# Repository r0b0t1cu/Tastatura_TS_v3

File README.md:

# Custom Keyboard for Turbo Spectrum

This is an open-source project for a mechanical keyboard compatible with the Romanian Turbo Spectrum computer: https://cobrasov.org/

The keyboard is designed to be easy to build, using accessible and commonly available components.
It also works with the classic ZX Spectrum, offering full compatibility with both systems.

# Keyboard PCB

The Gerber files are located in the production folder.

**Instructions for installing the required key switch libraries:**

Open the KiCad Plugin and Content Manager (PCM) and click Manage. Add a new entry with the plus button and paste the following URL:
https://raw.githubusercontent.com/ebastler/ebastler-KiCad-repository/main/repository.json

From now on, the "ebastler KiCad repository" will appear in your drop-down list, allowing you to easily install and update marbastlib directly through PCM — simple and hassle-free.

# Tastatură Custom pentru Turbo Spectrum

Acesta este un proiect open-source pentru o tastatură mecanică compatibilă cu computerul românesc **Turbo Spectrum**: https://cobrasov.org/
Tastatura a fost proiectată pentru a fi ușor de construit, utilizând componente accesibile.

Instructiuni pentru librariile de butoane folosite:
Open the KiCad "Plugin and Content Manager" (referred to as "PCM" from now on) and click on "Manage". Add a new entry with the plus sign and paste
https://raw.githubusercontent.com/ebastler/ebastler-KiCad-repository/main/repository.json
From this point on you will have "ebastler KiCad repository" in your drop-down selection, and it will allow you to install (and update) marbastlib through PCM - easy and hassle-free.

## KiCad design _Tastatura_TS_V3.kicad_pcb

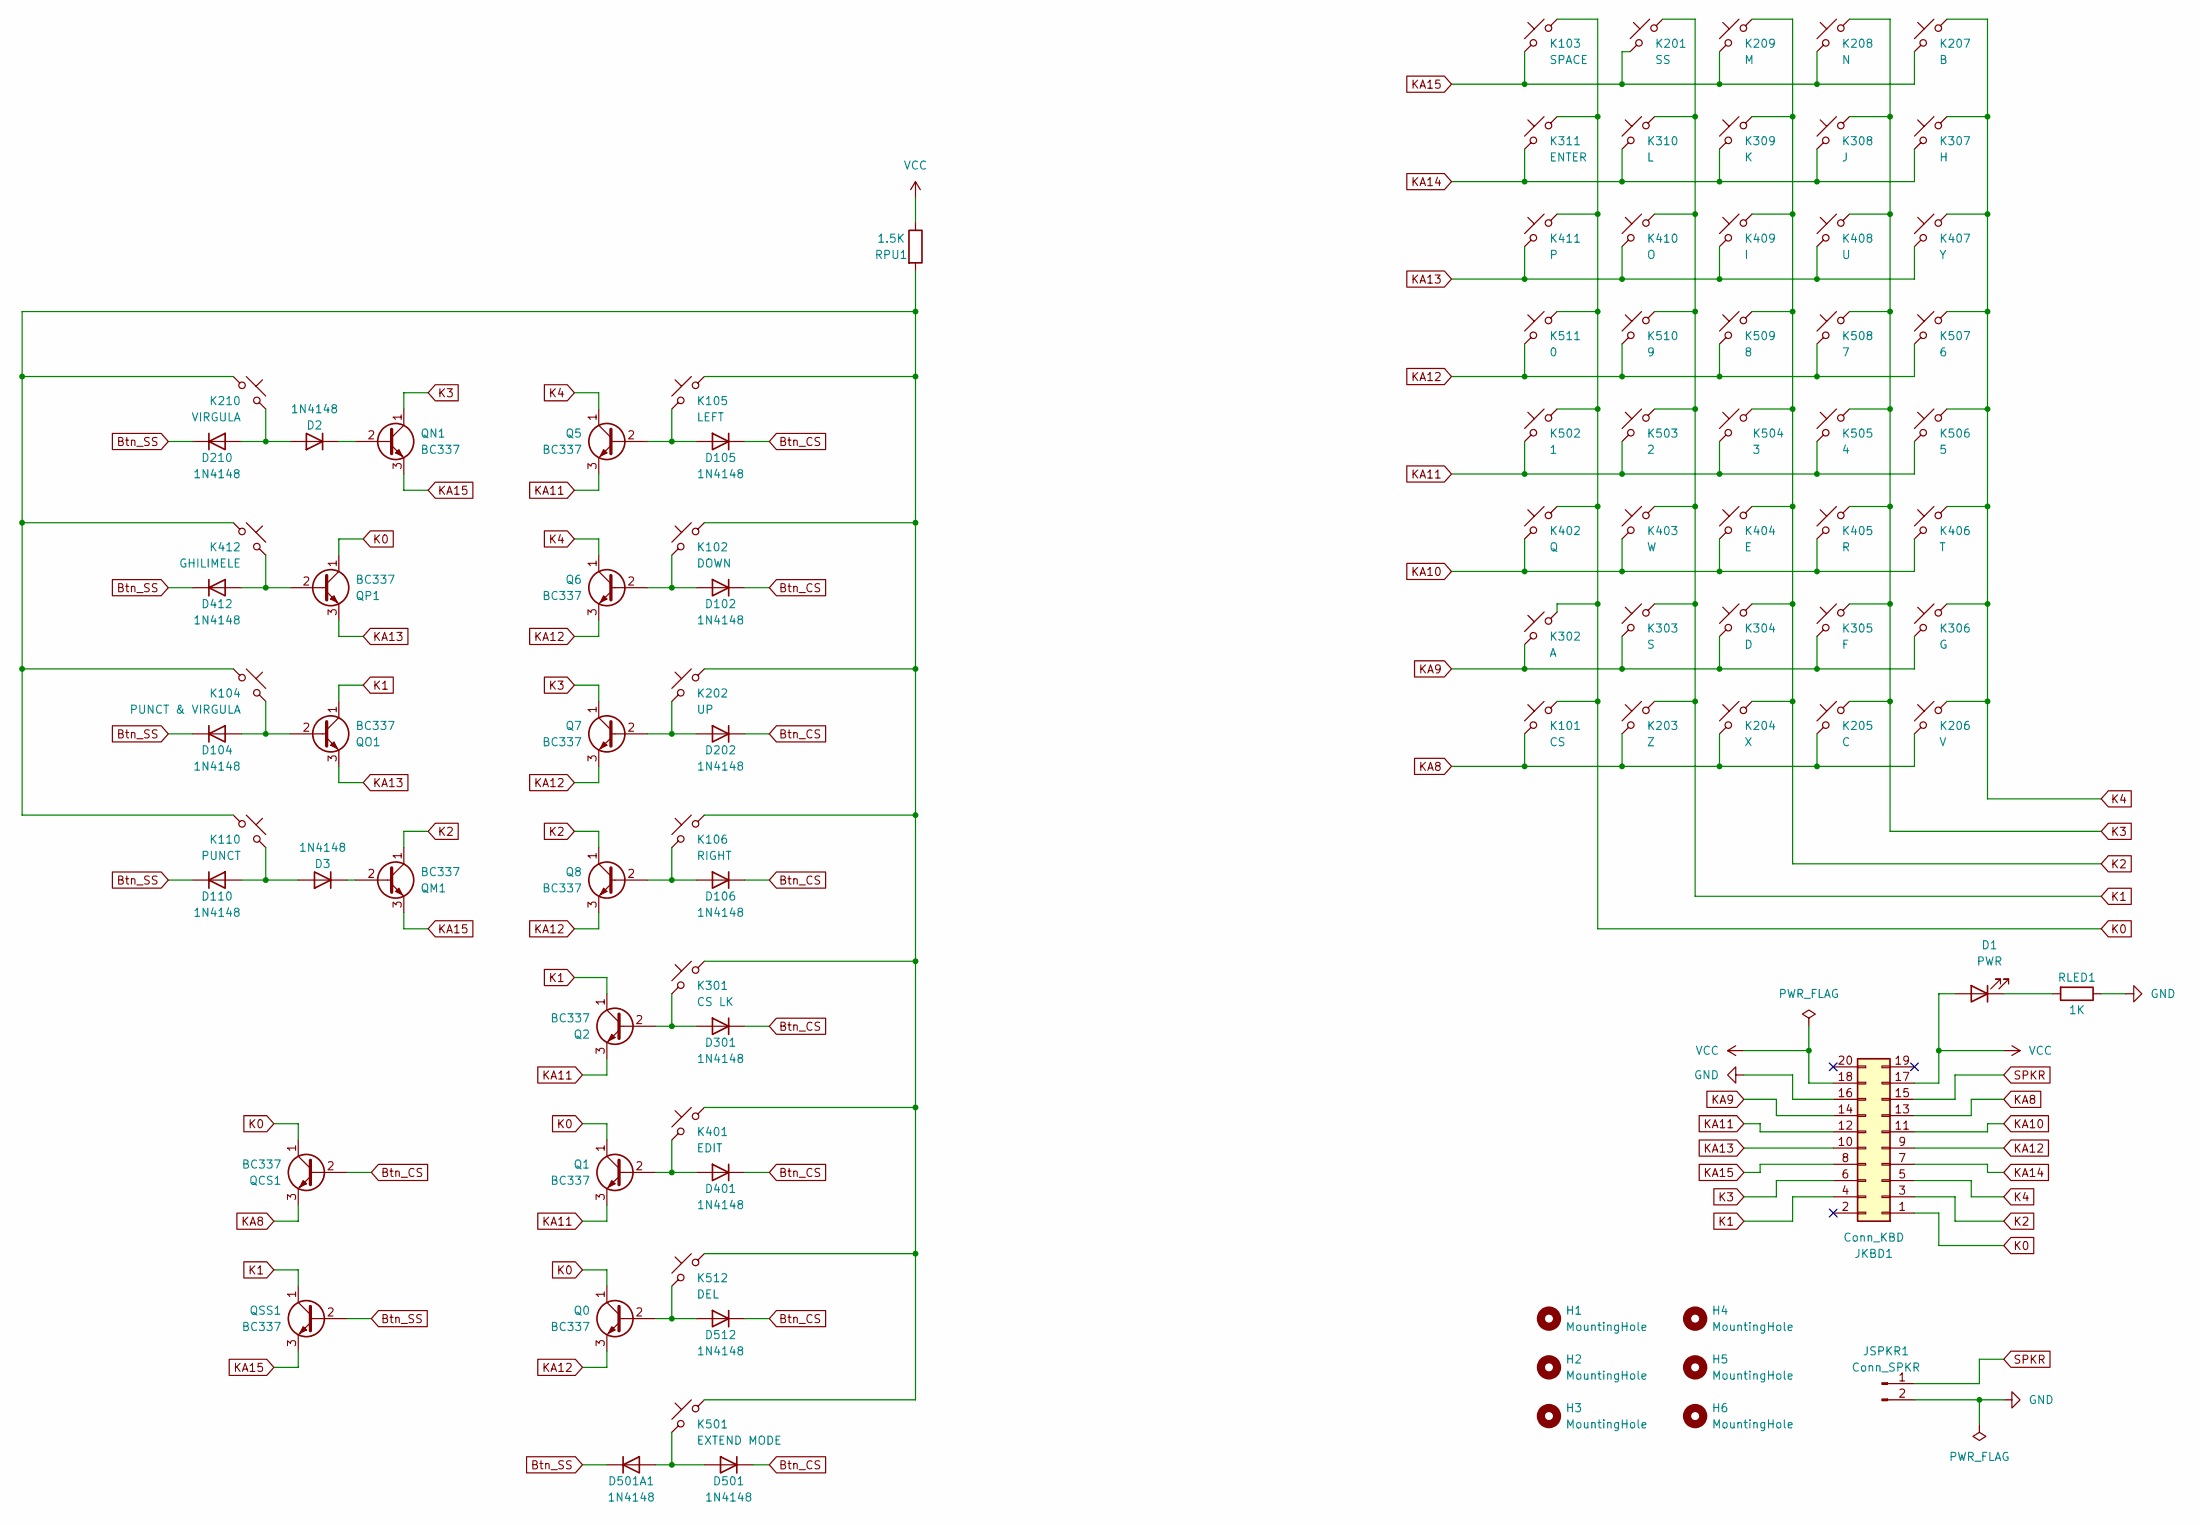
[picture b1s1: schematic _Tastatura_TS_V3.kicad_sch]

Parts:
D1: PWR; LED_D5.0mm
D2, D3, D102, D104, D105, D106, D110, D202, D210, D301, D401, D412, D501, D501A1, D512: 1N4148; D_DO-35_SOD27_P7.62mm_Horizontal
H1, H2, H3, H4, H5, H6: MountingHole; MountingHole_3.2mm_M3_Pad
JKBD1: Conn_KBD; IDC-Header_2x10_P2.54mm_Vertical
JSPKR1: Conn_SPKR; PinHeader_1x02_P2.54mm_Vertical
K101: CS; SW_Cherry_MX_2.25u_PCB
K102: DOWN; SW_Cherry_MX_1.00u_PCB
K103: SPACE; SW_Cherry_MX_6.25u_PCB
K104: PUNCT & VIRGULA; SW_Cherry_MX_1.00u_PCB
K105: LEFT; SW_Cherry_MX_1.00u_PCB
K106: RIGHT; SW_Cherry_MX_1.00u_PCB
K110: PUNCT; SW_Cherry_MX_1.00u_PCB
K201: SS; SW_Cherry_MX_1.75u_PCB
K202: UP; SW_Cherry_MX_1.00u_PCB
K203: Z; SW_Cherry_MX_1.00u_PCB
K204: X; SW_Cherry_MX_1.00u_PCB
K205: C; SW_Cherry_MX_1.00u_PCB
K206: V; SW_Cherry_MX_1.00u_PCB
K207: B; SW_Cherry_MX_1.00u_PCB
K208: N; SW_Cherry_MX_1.00u_PCB
K209: M; SW_Cherry_MX_1.00u_PCB
K210: VIRGULA; SW_Cherry_MX_1.00u_PCB
K301: CS LK; SW_Cherry_MX_1.50u_PCB
K302: A; SW_Cherry_MX_1.00u_PCB
K303: S; SW_Cherry_MX_1.00u_PCB
K304: D; SW_Cherry_MX_1.00u_PCB
K305: F; SW_Cherry_MX_1.00u_PCB
K306: G; SW_Cherry_MX_1.00u_PCB
K307: H; SW_Cherry_MX_1.00u_PCB
K308: J; SW_Cherry_MX_1.00u_PCB
K309: K; SW_Cherry_MX_1.00u_PCB
K310: L; SW_Cherry_MX_1.00u_PCB
K311: ENTER; SW_Cherry_MX_1.75u_PCB
K401: EDIT; SW_Cherry_MX_1.25u_PCB
K402: Q; SW_Cherry_MX_1.00u_PCB
K403: W; SW_Cherry_MX_1.00u_PCB
K404: E; SW_Cherry_MX_1.00u_PCB
K405: R; SW_Cherry_MX_1.00u_PCB
K406: T; SW_Cherry_MX_1.00u_PCB
K407: Y; SW_Cherry_MX_1.00u_PCB
K408: U; SW_Cherry_MX_1.00u_PCB
K409: I; SW_Cherry_MX_1.00u_PCB
K410: O; SW_Cherry_MX_1.00u_PCB
K411: P; SW_Cherry_MX_1.00u_PCB
K412: GHILIMELE; SW_Cherry_MX_1.25u_PCB
K501: EXTEND MODE; SW_Cherry_MX_1.00u_PCB
K502: 1; SW_Cherry_MX_1.00u_PCB
K503: 2; SW_Cherry_MX_1.00u_PCB
K504: 3; SW_Cherry_MX_1.00u_PCB
K505: 4; SW_Cherry_MX_1.00u_PCB
K506: 5; SW_Cherry_MX_1.00u_PCB
K507: 6; SW_Cherry_MX_1.00u_PCB
K508: 7; SW_Cherry_MX_1.00u_PCB
K509: 8; SW_Cherry_MX_1.00u_PCB
K510: 9; SW_Cherry_MX_1.00u_PCB
K511: 0; SW_Cherry_MX_1.00u_PCB
K512: DEL; SW_Cherry_MX_1.25u_PCB
Q0, Q1, Q2, Q5, Q6, Q7, Q8: BC337; TO-92_Wide
QCS1: BC337; TO-92_Wide
QM1: BC337; TO-92_Wide
QN1: BC337; TO-92_Wide
QO1: BC337; TO-92_Wide
QP1: BC337; TO-92_Wide
QSS1: BC337; TO-92_Wide
RLED1: 1K; R_Axial_DIN0207_L6.3mm_D2.5mm_P10.16mm_Horizontal
RPU1: 1.5K; R_Axial_DIN0207_L6.3mm_D2.5mm_P10.16mm_Horizontal

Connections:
Btn_CS: D102.1 (K), D105.1 (K), D106.1 (K), D202.1 (K), D301.1 (K), D401.1 (K), D501.1 (K), D512.1 (K), QCS1.2 (B)
Btn_SS: D104.1 (K), D110.1 (K), D210.1 (K), D412.1 (K), D501A1.1 (K), QSS1.2 (B)
GND: JKBD1.16, JSPKR1.2, RLED1.1
K0: JKBD1.1, K101.2, K103.2, K302.2, K311.2, K402.2, K411.2, K502.2, K511.2, Q0.1 (C), Q1.1 (C), QCS1.1 (C), QP1.1 (C)
K1: JKBD1.4, K201.2, K203.2, K303.2, K310.2, K403.2, K410.2, K503.2, K510.2, Q2.1 (C), QO1.1 (C), QSS1.1 (C)
K2: JKBD1.3, K204.2, K209.2, K304.2, K309.2, K404.2, K409.2, K504.2, K509.2, Q8.1 (C), QM1.1 (C)
K3: JKBD1.6, K205.2, K208.2, K305.2, K308.2, K405.2, K408.2, K505.2, K508.2, Q7.1 (C), QN1.1 (C)
K4: JKBD1.5, K206.2, K207.2, K306.2, K307.2, K406.2, K407.2, K506.2, K507.2, Q5.1 (C), Q6.1 (C)
KA8: JKBD1.13, K101.1, K203.1, K204.1, K205.1, K206.1, QCS1.3 (E)
KA9: JKBD1.14, K302.1, K303.1, K304.1, K305.1, K306.1
KA10: JKBD1.11, K402.1, K403.1, K404.1, K405.1, K406.1
KA11: JKBD1.12, K502.1, K503.1, K504.1, K505.1, K506.1, Q1.3 (E), Q2.3 (E), Q5.3 (E)
KA12: JKBD1.9, K507.1, K508.1, K509.1, K510.1, K511.1, Q0.3 (E), Q6.3 (E), Q7.3 (E), Q8.3 (E)
KA13: JKBD1.10, K407.1, K408.1, K409.1, K410.1, K411.1, QO1.3 (E), QP1.3 (E)
KA14: JKBD1.7, K307.1, K308.1, K309.1, K310.1, K311.1
KA15: JKBD1.8, K103.1, K201.1, K207.1, K208.1, K209.1, QM1.3 (E), QN1.3 (E), QSS1.3 (E)
unnamed: D1.1 (K), RLED1.2
unnamed: D2.2 (A), D210.2 (A), K210.2
unnamed: D2.1 (K), QN1.2 (B)
unnamed: D3.1 (K), QM1.2 (B)
unnamed: D102.2 (A), K102.2, Q6.2 (B)
unnamed: D104.2 (A), K104.2, QO1.2 (B)
unnamed: D105.2 (A), K105.2, Q5.2 (B)
unnamed: D106.2 (A), K106.2, Q8.2 (B)
unnamed: D3.2 (A), D110.2 (A), K110.2
unnamed: D202.2 (A), K202.2, Q7.2 (B)
unnamed: D301.2 (A), K301.2, Q2.2 (B)
unnamed: D401.2 (A), K401.2, Q1.2 (B)
unnamed: D412.2 (A), K412.2, QP1.2 (B)
unnamed: D501.2 (A), D501A1.2 (A), K501.2
unnamed: D512.2 (A), K512.2, Q0.2 (B)
unnamed: K102.1, K104.1, K105.1, K106.1, K110.1, K202.1, K210.1, K301.1, K401.1, K412.1, K501.1, K512.1, RPU1.2
SPKR: JKBD1.15, JSPKR1.1
VCC: D1.2 (A), JKBD1.17, JKBD1.18, RPU1.1

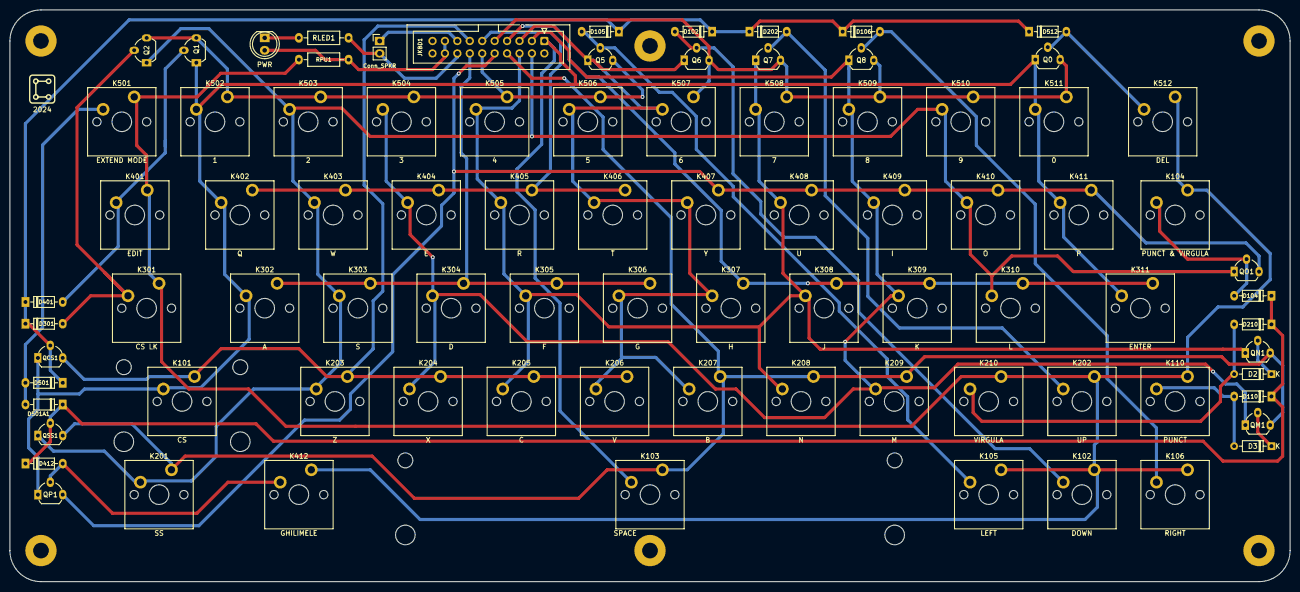
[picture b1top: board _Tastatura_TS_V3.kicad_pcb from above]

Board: 2 copper layers, 261.6 x 116.8 mm, 91 parts (0 on the bottom side), 34 nets.

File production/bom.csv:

Designator,Footprint,Quantity,Value,LCSC Part #
D1,LED_D5.0mm,1,PWR,
"D102, D104, D105, D106, D110, D2, D202, D210, D3, D301, D401, D412, D501, D501A1, D512",D_DO-35_SOD27_P7.62mm_Horizontal,15,1N4148,
JKBD1,IDC-Header_2x10_P2.54mm_Vertical,1,Conn_KBD,
JSPKR1,PinHeader_1x02_P2.54mm_Vertical,1,Conn_SPKR,
K101,SW_Cherry_MX_2.25u_PCB,1,CS,
K102,SW_Cherry_MX_1.00u_PCB,1,DOWN,
K103,SW_Cherry_MX_6.25u_PCB,1,SPACE,
K104,SW_Cherry_MX_1.00u_PCB,1,PUNCT & VIRGULA,
K105,SW_Cherry_MX_1.00u_PCB,1,LEFT,
K106,SW_Cherry_MX_1.00u_PCB,1,RIGHT,
K110,SW_Cherry_MX_1.00u_PCB,1,PUNCT,
K201,SW_Cherry_MX_1.75u_PCB,1,SS,
K202,SW_Cherry_MX_1.00u_PCB,1,UP,
K203,SW_Cherry_MX_1.00u_PCB,1,Z,
K204,SW_Cherry_MX_1.00u_PCB,1,X,
K205,SW_Cherry_MX_1.00u_PCB,1,C,
K206,SW_Cherry_MX_1.00u_PCB,1,V,
K207,SW_Cherry_MX_1.00u_PCB,1,B,
K208,SW_Cherry_MX_1.00u_PCB,1,N,
K209,SW_Cherry_MX_1.00u_PCB,1,M,
K210,SW_Cherry_MX_1.00u_PCB,1,VIRGULA,
K301,SW_Cherry_MX_1.50u_PCB,1,CS LK,
K302,SW_Cherry_MX_1.00u_PCB,1,A,
K303,SW_Cherry_MX_1.00u_PCB,1,S,
K304,SW_Cherry_MX_1.00u_PCB,1,D,
K305,SW_Cherry_MX_1.00u_PCB,1,F,
K306,SW_Cherry_MX_1.00u_PCB,1,G,
K307,SW_Cherry_MX_1.00u_PCB,1,H,
K308,SW_Cherry_MX_1.00u_PCB,1,J,
K309,SW_Cherry_MX_1.00u_PCB,1,K,
K310,SW_Cherry_MX_1.00u_PCB,1,L,
K311,SW_Cherry_MX_1.75u_PCB,1,ENTER,
K401,SW_Cherry_MX_1.25u_PCB,1,EDIT,
K402,SW_Cherry_MX_1.00u_PCB,1,Q,
K403,SW_Cherry_MX_1.00u_PCB,1,W,
K404,SW_Cherry_MX_1.00u_PCB,1,E,
K405,SW_Cherry_MX_1.00u_PCB,1,R,
K406,SW_Cherry_MX_1.00u_PCB,1,T,
K407,SW_Cherry_MX_1.00u_PCB,1,Y,
K408,SW_Cherry_MX_1.00u_PCB,1,U,
K409,SW_Cherry_MX_1.00u_PCB,1,I,
K410,SW_Cherry_MX_1.00u_PCB,1,O,
K411,SW_Cherry_MX_1.00u_PCB,1,P,
K412,SW_Cherry_MX_1.25u_PCB,1,GHILIMELE,
K501,SW_Cherry_MX_1.00u_PCB,1,EXTEND MODE,
K502,SW_Cherry_MX_1.00u_PCB,1,1,
K503,SW_Cherry_MX_1.00u_PCB,1,2,
K504,SW_Cherry_MX_1.00u_PCB,1,3,
K505,SW_Cherry_MX_1.00u_PCB,1,4,
K506,SW_Cherry_MX_1.00u_PCB,1,5,
K507,SW_Cherry_MX_1.00u_PCB,1,6,
K508,SW_Cherry_MX_1.00u_PCB,1,7,
K509,SW_Cherry_MX_1.00u_PCB,1,8,
K510,SW_Cherry_MX_1.00u_PCB,1,9,
K511,SW_Cherry_MX_1.00u_PCB,1,0,
K512,SW_Cherry_MX_1.25u_PCB,1,DEL,
"Q0, Q1, Q2, Q5, Q6, Q7, Q8, QCS1, QM1, QN1, QO1, QP1, QSS1",TO-92_Wide,13,BC337,
RLED1,R_Axial_DIN0207_L6.3mm_D2.5mm_P10.16mm_Horizontal,1,1K,
RPU1,R_Axial_DIN0207_L6.3mm_D2.5mm_P10.16mm_Horizontal,1,1.5K,

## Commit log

2025-12-04 Revise README for Turbo Spectrum keyboard project
    Updated README to improve clarity and add compatibility information.
2025-12-04 Update README with additional information and formatting
2025-12-04 Update README.md with improved formatting and clarity
